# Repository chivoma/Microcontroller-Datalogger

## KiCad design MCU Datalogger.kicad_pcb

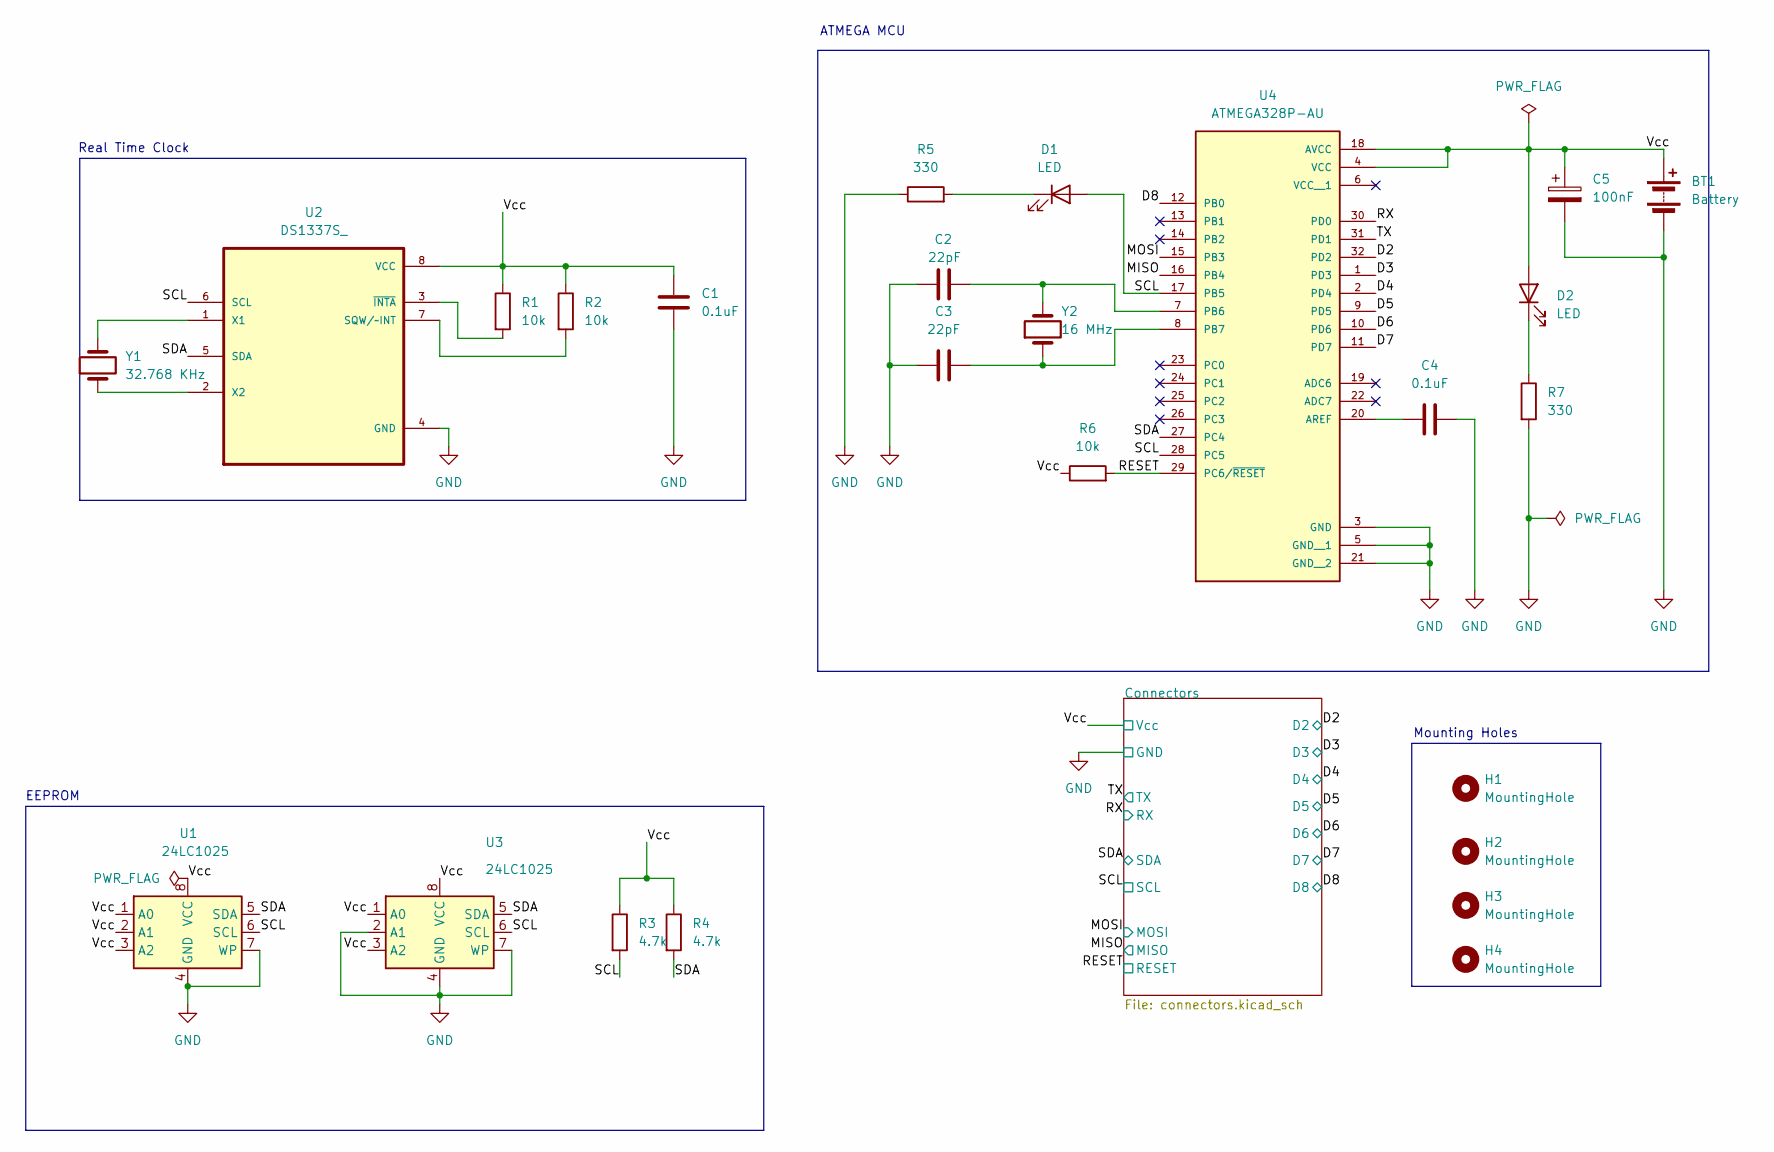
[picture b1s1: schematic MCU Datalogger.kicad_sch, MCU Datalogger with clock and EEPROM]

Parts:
BT1: Battery; PinHeader_1x02_P1.00mm_Vertical
C1, C4: 0.1uF; C_0805_2012Metric_Pad1.18x1.45mm_HandSolder
C2, C3: 22pF; C_0805_2012Metric_Pad1.18x1.45mm_HandSolder
C5: 100nF; C_0805_2012Metric_Pad1.18x1.45mm_HandSolder
D1, D2: LED; LED_0805_2012Metric_Pad1.15x1.40mm_HandSolder
H1, H2, H3, H4: MountingHole; MountingHole_2.1mm
R1, R2, R6: 10k; R_0805_2012Metric_Pad1.20x1.40mm_HandSolder
R3, R4: 4.7k; R_0805_2012Metric_Pad1.20x1.40mm_HandSolder
R5, R7: 330; R_0805_2012Metric_Pad1.20x1.40mm_HandSolder
U1, U3: 24LC1025; SOIC-8_5.23x5.23mm_P1.27mm
U2: DS1337S_; SOIC127P600X175-8N
U4: ATMEGA328P-AU; QFP80P900X900X120-32N; PARTREV 8271A
Y1: 32.768 KHz; Crystal_SMD_5032-2Pin_5.0x3.2mm_HandSoldering
Y2: 16 MHz; Crystal_SMD_5032-2Pin_5.0x3.2mm_HandSoldering

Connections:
/D2: U4.32 (PD2); also elsewhere on the board
/D3: U4.1 (PD3); also elsewhere on the board
/D4: U4.2 (PD4); also elsewhere on the board
/D5: U4.9 (PD5); also elsewhere on the board
/D6: U4.10 (PD6); also elsewhere on the board
/D7: U4.11 (PD7); also elsewhere on the board
/D8: U4.12 (PB0); also elsewhere on the board
/MISO: U4.16 (PB4); also elsewhere on the board
/MOSI: U4.15 (PB3); also elsewhere on the board
/RESET: R6.2, U4.29 (PC6/~RESET); also elsewhere on the board
/RX: U4.30 (PD0); also elsewhere on the board
/SCL: D1.2 (A), R3.2, U1.6 (SCL), U2.6 (SCL), U3.6 (SCL), U4.17 (PB5), U4.28 (PC5); also elsewhere on the board
/SDA: R4.2, U1.5 (SDA), U2.5 (SDA), U3.5 (SDA), U4.27 (PC4); also elsewhere on the board
/TX: U4.31 (PD1); also elsewhere on the board
/Vcc: BT1.1 (+), C1.1, C5.1, D2.2 (A), R1.1, R2.1, R3.1, R4.1, R6.1, U1.1 (A0), U1.2 (A1), U1.3 (A2), U1.8 (VCC), U2.8 (VCC), U3.1 (A0), U3.3 (A2), U3.8 (VCC), U4.4 (VCC), U4.18 (AVCC); also elsewhere on the board
GND: BT1.2 (-), C1.2, C2.1, C3.1, C4.2, C5.2, R5.1, R7.2, U1.4 (GND), U1.7 (WP), U2.4 (GND), U3.2 (A1), U3.4 (GND), U3.7 (WP), U4.3 (GND), U4.5 (GND__1), U4.21 (GND__2); also elsewhere on the board
unnamed: D1.1 (K), R5.2
unnamed: D2.1 (K), R7.1
unnamed: R2.2, U2.7 (SQW/~INT)
unnamed: U2.1 (X1), Y1.2
unnamed: U2.2 (X2), Y1.1
unnamed: R1.2, U2.3 (~INTA)
unnamed: C4.1, U4.20 (AREF)
unnamed: C2.2, U4.7 (PB6), Y2.2
unnamed: C3.2, U4.8 (PB7), Y2.1

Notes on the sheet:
Mounting Holes
EEPROM
ATMEGA MCU
Real Time Clock

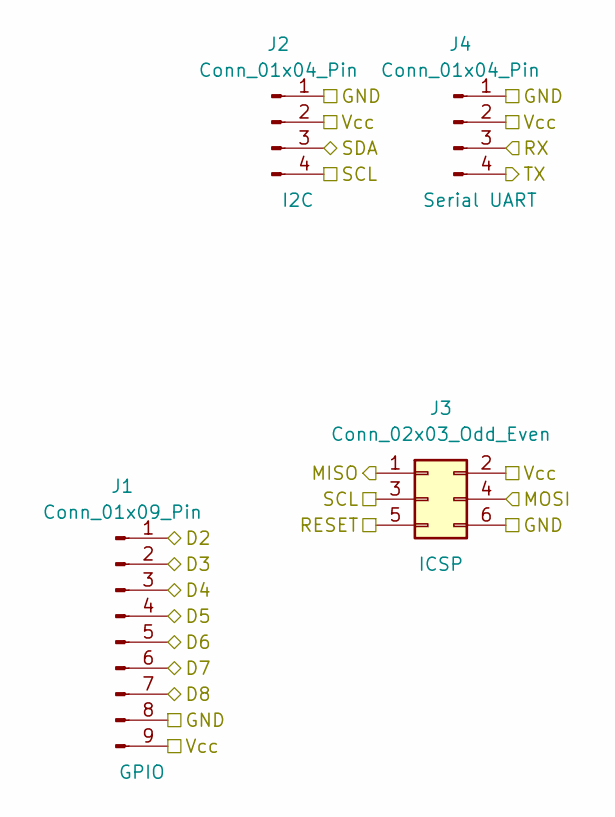
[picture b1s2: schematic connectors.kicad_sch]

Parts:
J1: Conn_01x09_Pin; PinHeader_1x09_P2.54mm_Vertical
J2, J4: Conn_01x04_Pin; PinHeader_1x04_P2.54mm_Vertical
J3: Conn_02x03_Odd_Even; PinHeader_2x03_P2.54mm_Vertical

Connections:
/D2: J1.1; also elsewhere on the board
/D3: J1.2; also elsewhere on the board
/D4: J1.3; also elsewhere on the board
/D5: J1.4; also elsewhere on the board
/D6: J1.5; also elsewhere on the board
/D7: J1.6; also elsewhere on the board
/D8: J1.7; also elsewhere on the board
/MISO: J3.1; also elsewhere on the board
/MOSI: J3.4; also elsewhere on the board
/RESET: J3.5; also elsewhere on the board
/RX: J4.3; also elsewhere on the board
/SCL: J2.4, J3.3; also elsewhere on the board
/SDA: J2.3; also elsewhere on the board
/TX: J4.4; also elsewhere on the board
/Vcc: J1.9, J2.2, J3.2, J4.2; also elsewhere on the board
GND: J1.8, J2.1, J3.6, J4.1; also elsewhere on the board

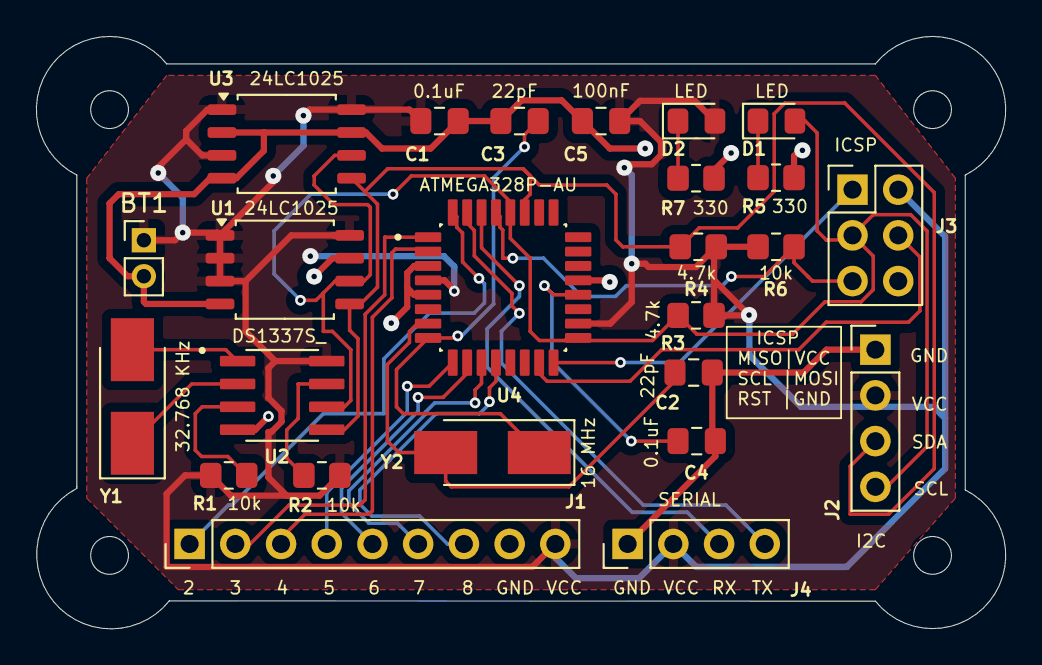
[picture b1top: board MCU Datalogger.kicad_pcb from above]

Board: 2 copper layers, 53.8 x 32.9 mm, 29 parts (0 on the bottom side), 25 nets.

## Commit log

2024-09-26 MCU Datalogger Commit
2024-09-26 Add .gitignore file
2024-09-26 EEschema Setup
2024-09-26 added required symbols
2024-09-26 changed location of components
2024-09-26 added component values
2024-09-26 Added 3rd party footprints
2024-09-26 Wired the main schematic
2024-09-26 Wired connectors sheet
2024-09-27 Completed Schematics and worked on comments
2024-09-27 Setup Pcbnew
2024-09-28 design change
2024-10-01 Finished Routing PCB Tracks
2024-10-01 refined board outline
2024-10-02 Filled the GND zones
2024-10-04 Refined the tracks outline
2024-10-05 Finished routing, silkscreen setup of the 2layer pcb
2024-10-06 Added final design changes
2024-10-07 Added gitattributes file to ignore pcb file when merged
2024-10-08 Fixed errors in the schematic
2024-10-08 Design fix
